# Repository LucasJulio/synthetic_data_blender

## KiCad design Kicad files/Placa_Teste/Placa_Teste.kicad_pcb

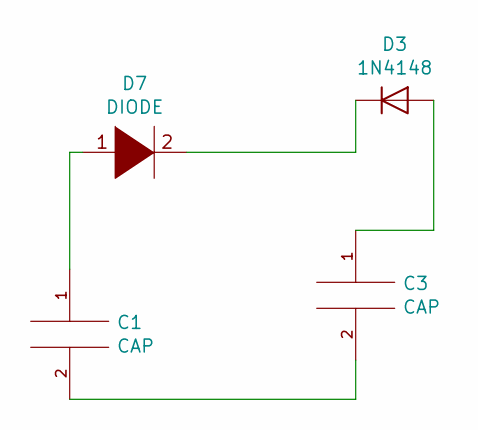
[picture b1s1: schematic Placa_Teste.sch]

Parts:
C1: CAP; C_Radial_D5.0mm_H11.0mm_P2.00mm
C3: CAP; C_Radial_D4.0mm_H5.0mm_P1.50mm
D3: 1N4148; D_DO-35_SOD27_P7.62mm_Horizontal
D7: DIODE; D_5W_P5.08mm_Vertical_AnodeUp

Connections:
unnamed: C1.1, D7.1 (K)
unnamed: C1.2, C3.2
unnamed: C3.1, D3.2 (A)
unnamed: D3.1 (K), D7.2 (A)

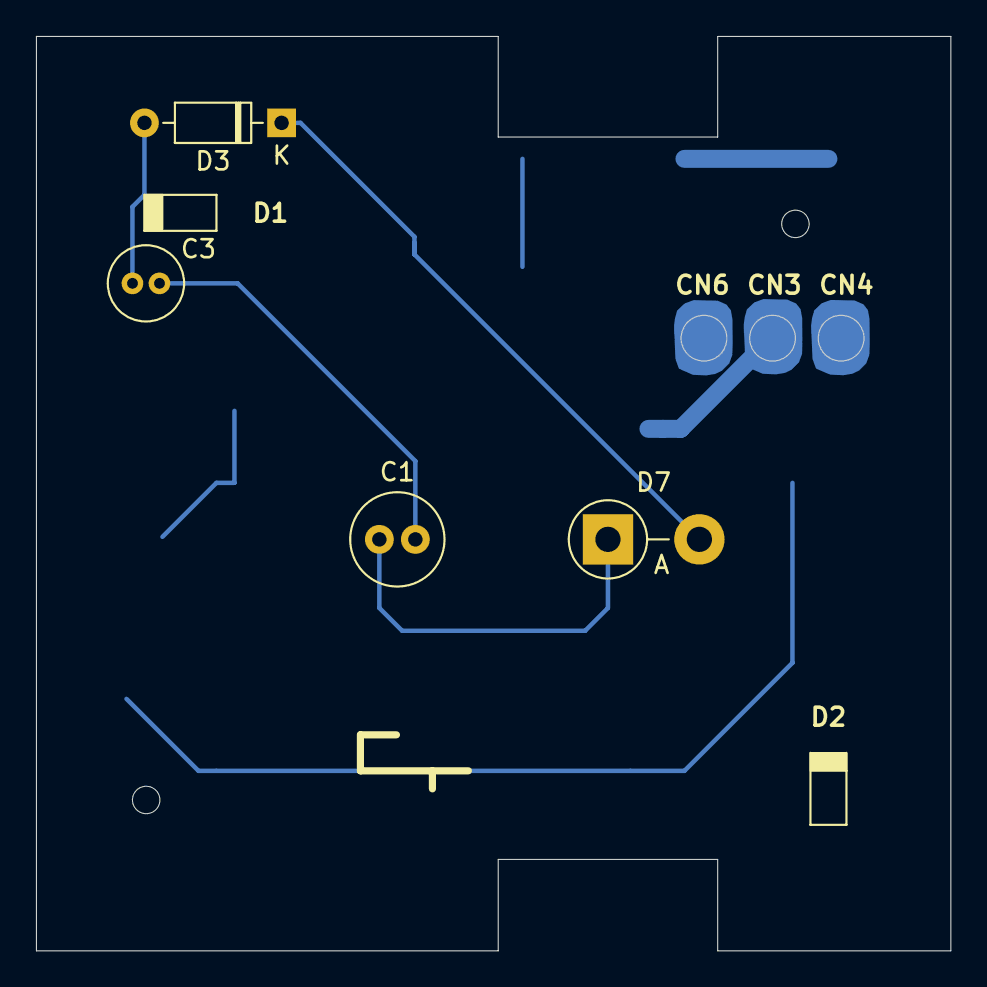
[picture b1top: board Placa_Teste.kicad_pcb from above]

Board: 2 copper layers, 50.8 x 50.8 mm, 4 parts (0 on the bottom side), 4 nets.

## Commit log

2020-02-16 Some randomization with camera tracking
    Known issues:
    - PCB gets "dismembered" halfway through
    - Textures are still ugly
    - Could add some "zoom" randomization maybe?
    - Not sure if the camera is following the bezier curve trajectory
2020-02-17 Better names; exposure, and focal length can now be set
2020-07-13 Added some neural_network samples
2020-07-17 Arquivos Kicad e .blend com silkscreen
2020-07-18 Atualizando arquivos kicad e .blender
2020-07-18 "dataset" bringup
    - Introduced "datasets" folder with a "sample_dataset" showing how files should be structured
    - Minor changes to the colors rendered in labels: this was necessary for converting the "humanly readable" label maps to "neural network-friendly" maps
2020-07-18 Adição de shader translucido
2020-07-19 Using realistic PCB model to generate renders manually
2020-07-19 Script running to generate renders automatically, still minor issues
    Had to remove translation over objects of interest, since they were creating problematic renders
2020-07-20 Git ignoring .png files from now on
2020-07-20 First PCB semantic segmentation neural network train working
2020-07-21 Major improvements to training script; Repository cleanup
    - Increased input size of models
    - Implemented mild data augmentation
    - Better overall hyper-parameters
    - Added some more examples to PCB_v1 dataset annotations
    - Cleaned up some old files from repo
2020-07-22 Added short demonstration using Webcam
2020-09-25 Adição do modelo do Arduino
2020-10-09 Script para fornecimento de IDs de segmentação para objetos
2020-10-09 Mudança do conector da fonte do arduino
2020-10-10 implementação de método para iluminação usando imagens HDRI e adição de textura ao plano
2020-10-10 Adicionando alguns HDR
2020-10-11 Adicionado mudança de fundo, sumir componentes, rotacao e posicao de camera e inclusao de aleatoriedade de texturas
2020-10-11 funcionando
2020-10-11 sem print incomodando
2020-10-11 Revert "sem print incomodando"
    This reverts commit 10a280cfa98fbc1c8fb857d532d5124661f60b9b.
2020-10-11 Texturas arruamadas
2020-10-11 Atmel não estava parentado com seu conector
2020-10-11 Correção do funcionamento das luzes de suporte
2020-10-11 Correção dos nomes de arquivos
2020-10-11 Sumir Componentes funcionando e adição de uma textura nova
2020-10-11 Corrigido gitignore
    Não ignora .pngs mais
2020-10-11 Texturas do substrato e tentativa de funcionar a sumida de componentes
2020-10-13 Arduino "model train" operational
2020-10-17 Repo cleanup; changes to train script
    - Removed unused files
    - Train with some changes
2020-11-19 New textures; 'hide_components' works; Better camera angles
    - Added lots of new textures to be used as background plane
    - Conditional hidden components and texts now working
    - Camera angles now more favorable
    - Camera closer to object
    - Simplified 'current_script.py'
2020-11-21 Improved deploy scripts; changes to training
    - Added scripts to deploy selected models using webcams or image files
    - Deploy scripts now show segmentations in colored images
    - Using sparse categorical focal loss as training loss
    - Model results are saved in timestamped directories
2020-11-22 Melhorias do modelo 3D
    OBS: Acrecréscimo de aleatoriedade na cor do Arduino
2020-11-22 Melhorias no modelo 3D
2020-11-22 update do arquivo blender
2020-11-23 Reorganized code
    - Scripts organized by their purposes
    - Many scripts renamed for clarity
    - Deploy scripts
2020-11-23 Added EarlyStopping callback; no more "leaking" RAM
    - EarlyStopping callback during training
    - Cleaner training script (moved inference and normalization to utils)
    - Rendering script now keeps camera still and has many different light sources
2020-11-26 Better 3D model rendering; TensorBoard operational; Cleaner code
    Train:
    - Added ReduceLROnPlateau callback
    - Added Images callback
    - Training loop implemented
    - Models saved with timestamps
    - Added Hyperparameters and Metrics tracking
2020-11-28 More HPs, metrics and regularizations
    Train:
    - More hyperparameters and metrics (see below)
    - Model folders and training logs now have the same unique ID (corresponding to Trial ID in Tensorboard's Hyperparameters) given by a timestamp
    Hyperparameters and Metrics:
    - Adjustments to hyperparameters values
    - Added Crossentropy metric
2020-12-12 deploy_on_webcam: now shows comparisons between model and ground truth
    - Many other changes that should be documented later on!
2020-12-12 Better deploy software
